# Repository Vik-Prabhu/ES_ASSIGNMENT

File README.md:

## Buy Links to the modules used
- [HX711 IC](https://evelta.com/24bit-5v-analog-to-digital-converter-adc/?utm_source=google&utm_campaign=20308067004&utm_medium=cpc&utm_content=&utm_term=&gad_source=1&gad_campaignid=20317564702&gclid=CjwKCAjw3MXBBhAzEiwA0vLXQdyyDHSwxgKj9gFQ3dmok80FhPgFMVpN6XNjl5bAlBoQQgoylnZ6_xoCdvAQAvD_BwE)
- [TMP117](https://robu.in/product/smartelex-high-precision-temperature-sensor-tmp117/)
- [2.42in OLED](https://robu.in/product/waveshare-2-42inch-oled-display-module-128x64-resolution-spi-i2c-communication/?gad_source=1&gad_campaignid=17416544847&gclid=CjwKCAjw3MXBBhAzEiwA0vLXQShEqZQmIAbbxoL2zqc6n8CxB_1R80dxRqqmuzw0wwDo_gFpXzo7MxoCHSYQAvD_BwE)
- [Optical Encoder](https://robu.in/product/orange-1000-ppr-ab-phase-incremental-optical-rotary-encoder/)
- [MicroSD Card Reader Module](https://robu.in/product/micro-sd-card-module/#tab-specification)
- [WCS1700 Module](https://robu.in/product/wcs1700-hall-current-sensor-with-over-current-protection/?gad_source=1&gad_campaignid=20363337560&gclid=CjwKCAjw3MXBBhAzEiwA0vLXQURRCuQeek4KpJJgWQCjVowMEDX3MaXc_5YCE4EgV_5W4Gc9HrqNEhoC97cQAvD_BwE)

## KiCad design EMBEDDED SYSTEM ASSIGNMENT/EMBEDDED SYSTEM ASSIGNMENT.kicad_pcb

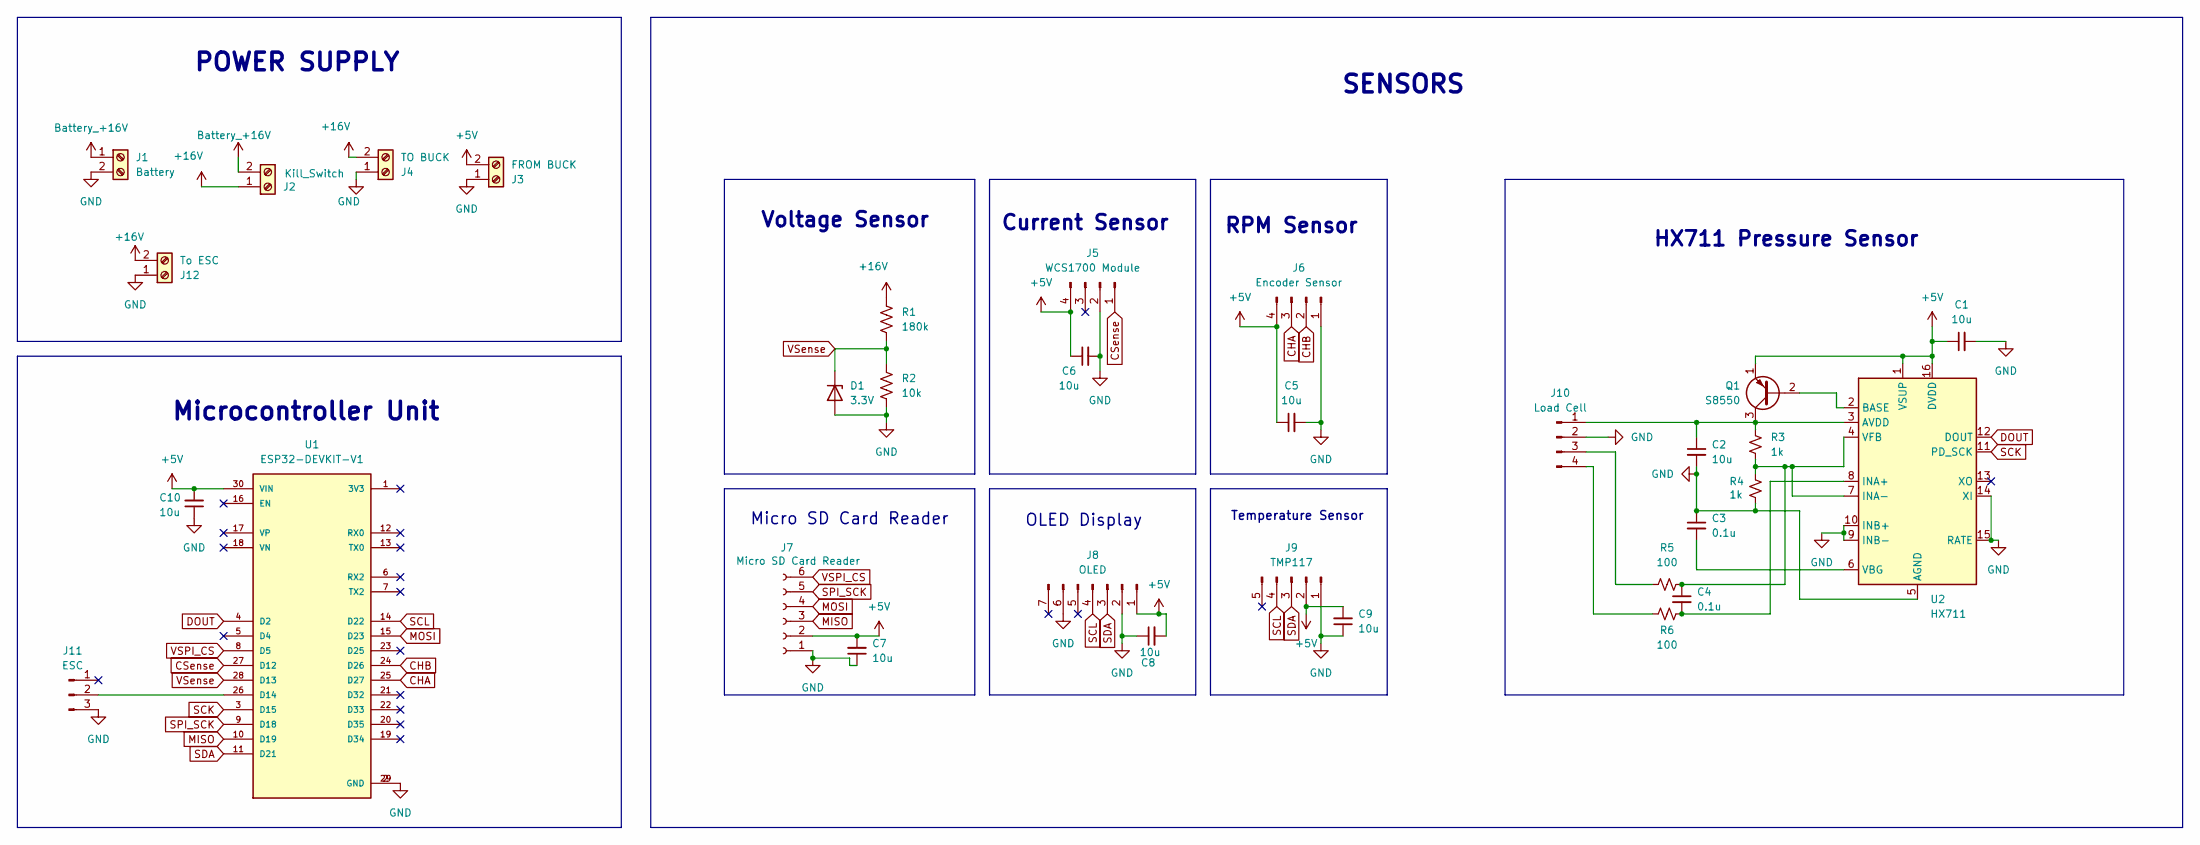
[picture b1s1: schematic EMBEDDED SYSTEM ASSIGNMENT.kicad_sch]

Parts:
C1, C2, C5, C6, C7, C8, C9, C10: 10u; C_0805_2012Metric
C3, C4: 0.1u; C_0805_2012Metric
D1: 3.3V; D_0805_2012Metric
J1: Battery; AMASS_XT60PW-M_1x02_P7.20mm_Horizontal
J2: Kill_Switch; AMASS_XT60PW-M_1x02_P7.20mm_Horizontal
J3: FROM BUCK; AMASS_XT60PW-M_1x02_P7.20mm_Horizontal
J4: TO BUCK; AMASS_XT60PW-M_1x02_P7.20mm_Horizontal
J5: WCS1700 Module; JST_XH_B4B-XH-A_1x04_P2.50mm_Vertical
J6: Encoder Sensor; JST_XH_B4B-XH-A_1x04_P2.50mm_Vertical
J7: Micro SD Card Reader; JST_XH_B6B-XH-A_1x06_P2.50mm_Vertical
J8: OLED; JST_XH_B7B-XH-A_1x07_P2.50mm_Vertical
J9: TMP117; JST_XH_B5B-XH-A_1x05_P2.50mm_Vertical
J10: Load Cell; JST_XH_B4B-XH-A_1x04_P2.50mm_Vertical
J11: ESC; JST_XH_B3B-XH-A_1x03_P2.50mm_Vertical
J12: To ESC; AMASS_XT60PW-M_1x02_P7.20mm_Horizontal
Q1: S8550; SOT-23
R1: 180k; R_0805_2012Metric
R2: 10k; R_0805_2012Metric
R3, R4: 1k; R_0805_2012Metric
R5, R6: 100; R_0805_2012Metric
U1: ESP32-DEVKIT-V1; MODULE_ESP32_DEVKIT_V1; PARTREV N/A
U2: HX711; SOP-16_3.9x9.9mm_P1.27mm

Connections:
+5V: C1.1, C5.1, C6.1, C7.2, C8.2, C9.2, C10.2, J3.2, J5.4, J6.4, J7.2, J8.1, J9.2, Q1.1 (E), U1.30 (VIN), U2.1 (VSUP), U2.16 (DVDD)
+16V: J2.1, J4.2, J12.2, R1.1
Battery_+16V: J1.1, J2.2
CHA: J6.3, U1.25 (D27)
CHB: J6.2, U1.24 (D26)
CSense: J5.1, U1.27 (D12)
DOUT: U1.4 (D2), U2.12 (DOUT)
GND: C1.2, C2.2, C3.1, C5.2, C6.2, C7.1, C8.1, C9.1, C10.1, D1.2 (A), J1.2, J3.1, J4.1, J5.2, J6.1, J7.1, J8.2, J8.6, J9.1, J10.2, J11.3, J12.1, R2.2, R4.2, U1.2 (GND), U1.29 (GND), U2.5 (AGND), U2.9 (INB-), U2.10 (INB+), U2.14 (XI), U2.15 (RATE)
MISO: J7.3, U1.10 (D19)
MOSI: J7.4, U1.15 (D23)
unnamed: C2.1, J10.1, Q1.3 (C), R3.1, U2.3 (AVDD)
unnamed: J10.3, R5.1
unnamed: J10.4, R6.1
unnamed: J11.2, U1.26 (D14)
unnamed: Q1.2 (B), U2.2 (BASE)
unnamed: C4.2, R6.2, U2.8 (INA+)
unnamed: C4.1, R3.2, R4.1, R5.2, U2.4 (VFB), U2.7 (INA-)
unnamed: C3.2, U2.6 (VBG)
SCK: U1.3 (D15), U2.11 (PD_SCK)
SCL: J8.4, J9.4, U1.14 (D22)
SDA: J8.3, J9.3, U1.11 (D21)
SPI_SCK: J7.5, U1.9 (D18)
VSPI_CS: J7.6, U1.8 (D5)
VSense: D1.1 (K), R1.2, R2.1, U1.28 (D13)

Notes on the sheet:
Temperature Sensor
Microcontroller Unit
SENSORS
OLED Display
HX711 Pressure Sensor
Micro SD Card Reader
RPM Sensor
POWER SUPPLY
Current Sensor
Voltage Sensor

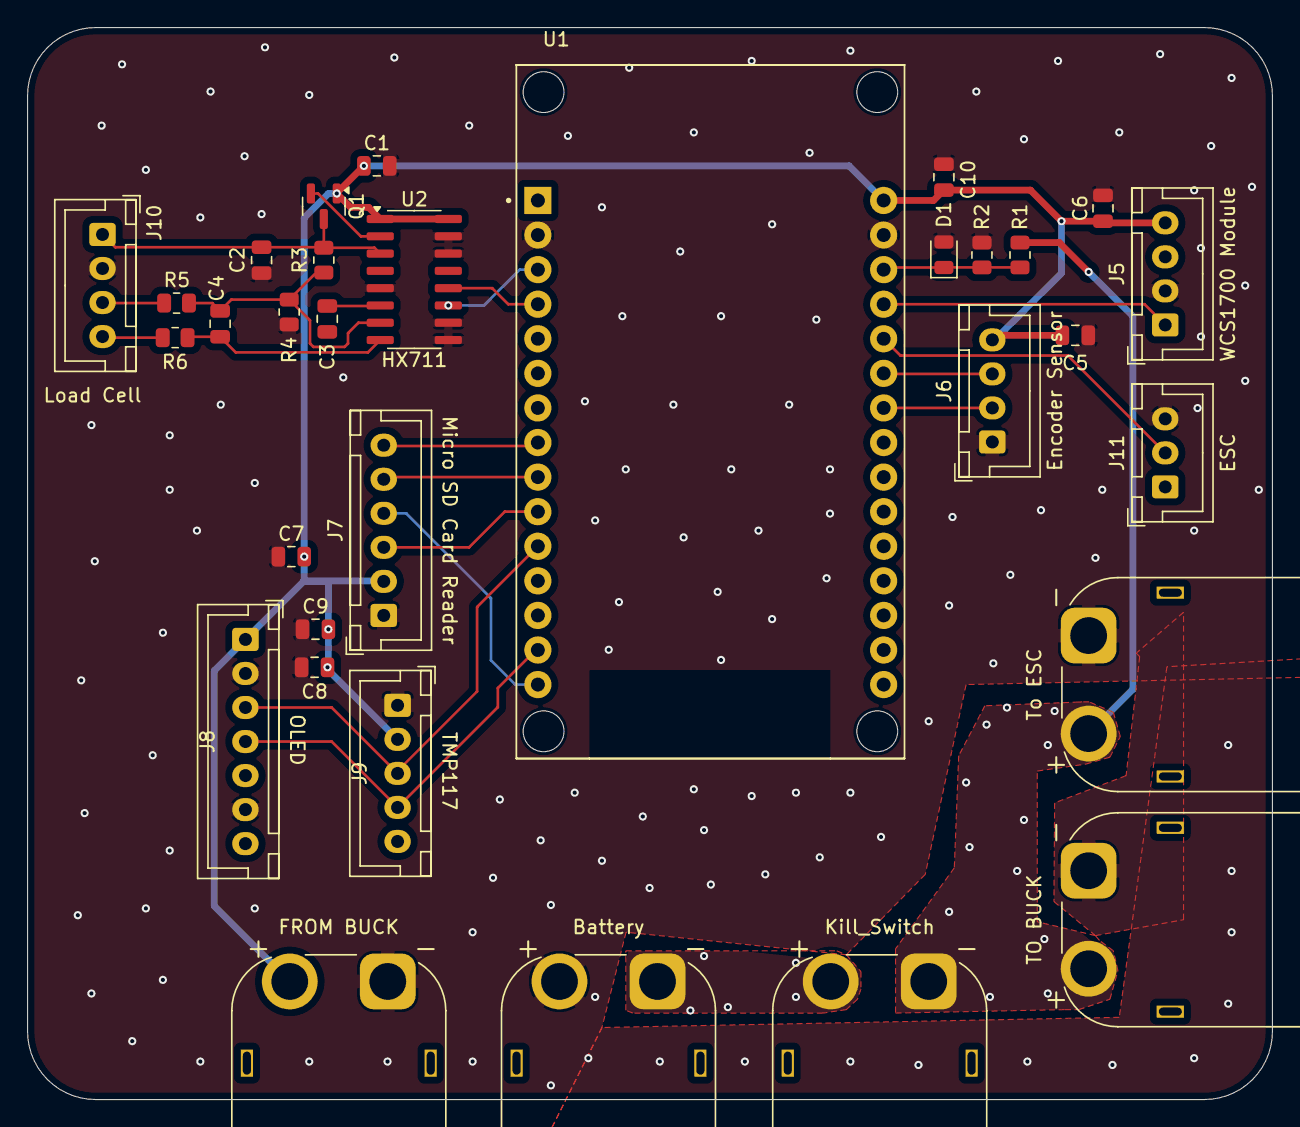
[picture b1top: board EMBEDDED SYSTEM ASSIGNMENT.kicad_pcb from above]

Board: 2 copper layers, 91.4 x 78.7 mm, 32 parts (0 on the bottom side), 24 nets.

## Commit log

2025-05-24 inital commit
2025-05-24 Final touches
2025-05-24 Update .gitignore and remove ignored files
2025-05-25 errors resolved
